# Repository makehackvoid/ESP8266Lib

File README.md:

ESP8266Lib
----------

This is MHV's library for the ESP8266. It's a group effort
and aims to make developing for the ESP8266 a little easier.

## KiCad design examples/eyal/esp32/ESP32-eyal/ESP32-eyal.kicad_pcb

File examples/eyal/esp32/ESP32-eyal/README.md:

I decided to make a PCB for my ESP32 things. I have many installed, each made differently. It is time to standardise them, hence this KiCAD (6) project.
======

I had the boards made by JLCPCB on 29/Feb/24, see the gerbers: gerbers-20240229-1703.zip

WARNING: Two issues with this version:
```
    1 - Solar charger requires a cap on the input.
    2 - The I2C lines incorrectly connect to pins 21/22, should be GPIO 21/22 (pins 33[SDA]/36[SCL]).
```

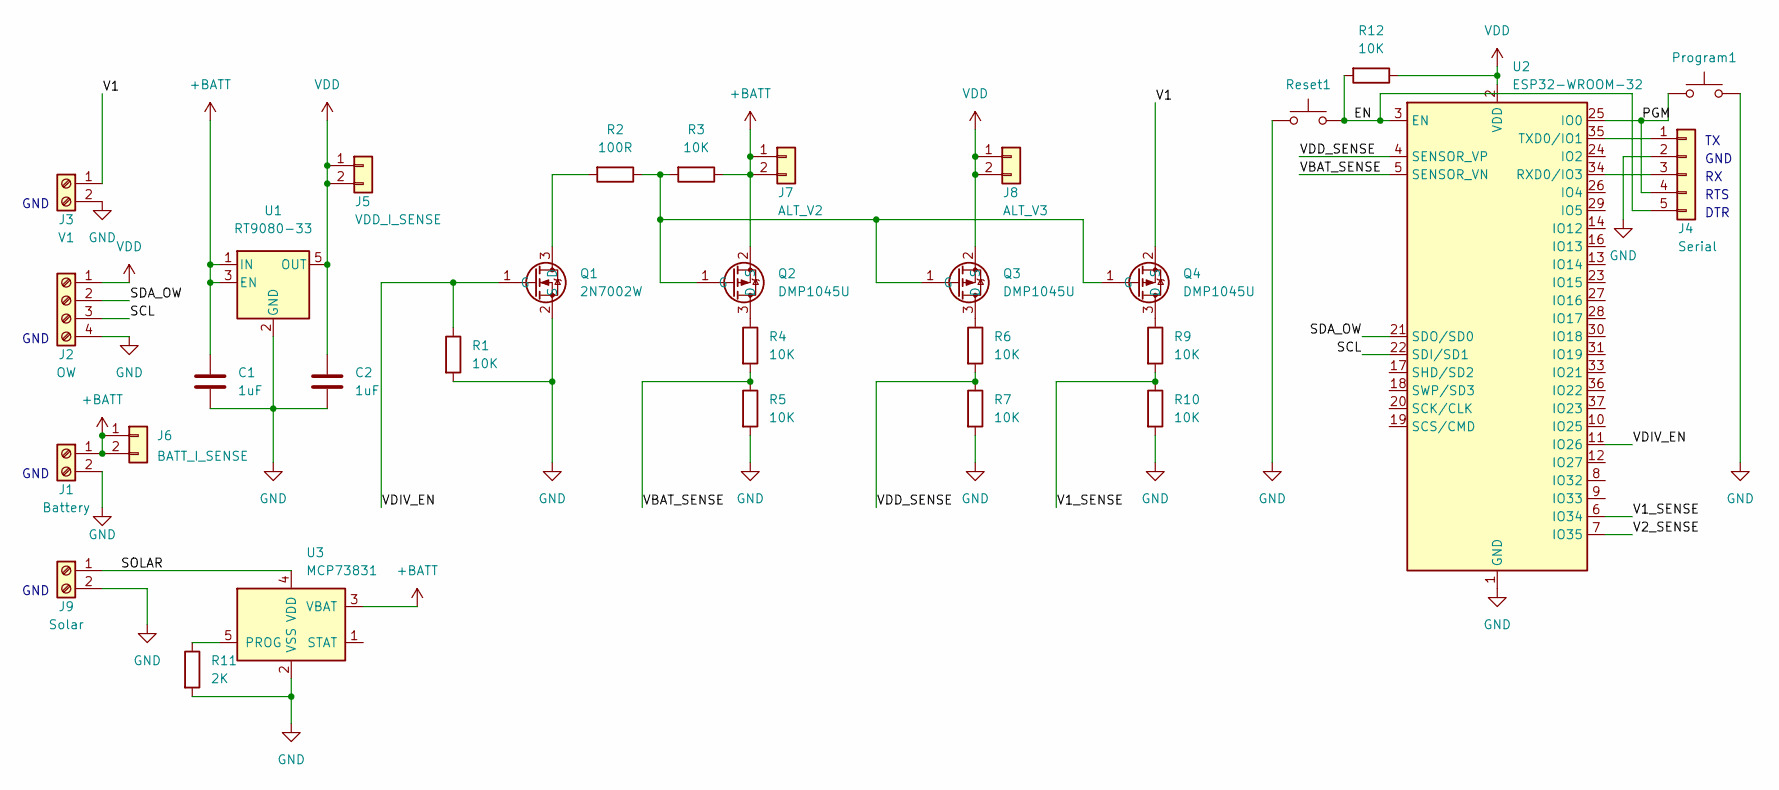
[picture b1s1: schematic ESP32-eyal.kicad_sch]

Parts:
C1, C2: 1uF; C_0805_2012Metric
J1: Battery; TerminalBlock_TE_282834-2_1x02_P2.54mm_Horizontal
J2: OW; TerminalBlock_TE_282834-4_1x04_P2.54mm_Horizontal
J3: V1; TerminalBlock_TE_282834-2_1x02_P2.54mm_Horizontal
J4: Serial; PinHeader_1x05_P2.54mm_Vertical
J5: VDD_I_SENSE; PinHeader_1x02_P2.54mm_Vertical
J6: BATT_I_SENSE; PinHeader_1x02_P2.54mm_Vertical
J7: ALT_V2; PinHeader_1x02_P2.54mm_Vertical
J8: ALT_V3; PinHeader_1x02_P2.54mm_Vertical
J9: Solar; TerminalBlock_TE_282834-2_1x02_P2.54mm_Horizontal
Program1: SW_Push; My_Switch
Q1: 2N7002W; SOT-23
Q2, Q3, Q4: DMP1045U; SOT-23
R1, R3, R4, R5, R6, R7, R9, R10, R12: 10K; R_0805_2012Metric
R2: 100R; R_0805_2012Metric
R11: 2K; R_0805_2012Metric
Reset1: SW_Push; My_Switch
U1: RT9080-33; SOT-23-5
U2: ESP32-WROOM-32
U3: MCP73831; SOT-23-5

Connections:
+BATT: C1.1, J1.1, J6.1, J6.2, J7.1, J7.2, Q2.2 (S), R3.1, U1.1 (IN), U1.3 (EN), U3.3 (VBAT)
/EN: J4.5, R12.2, Reset1.2, U2.3 (EN); also elsewhere on the board
/PGM: J4.4, Program1.1, U2.25 (IO0); also elsewhere on the board
/SCL: J2.3, U2.22 (SDI/SD1)
/SDA_OW: J2.2, U2.21 (SDO/SD0)
/SOLAR: J9.1, U3.4 (VDD); also elsewhere on the board
/V1: J3.1, Q4.2 (S)
/V1_SENSE: R9.2, R10.1, U2.6 (IO34)
/V2_SENSE: U2.7 (IO35)
/VBAT_SENSE: R4.2, R5.1, U2.5 (SENSOR_VN)
/VDD_SENSE: R6.2, R7.1, U2.4 (SENSOR_VP)
/VDIV_EN: Q1.1 (G), R1.1, U2.11 (IO26)
GND: C1.2, C2.2, J1.2, J2.4, J3.2, J4.2, J9.2, Program1.2, Q1.2 (S), R1.2, R5.2, R7.2, R10.2, R11.2, Reset1.1, U1.2 (GND), U2.1 (GND), U2.15 (GND), U2.38 (GND), U2.39 (GND), U3.2 (VSS); also elsewhere on the board
unnamed: J4.1, U2.35 (TXD0/IO1)
unnamed: J4.3, U2.34 (RXD0/IO3)
unnamed: Q1.3 (D), R2.2
unnamed: Q2.1 (G), Q3.1 (G), Q4.1 (G), R2.1, R3.2
unnamed: Q2.3 (D), R4.1
unnamed: Q3.3 (D), R6.1
unnamed: Q4.3 (D), R9.1
unnamed: R11.1, U3.5 (PROG)
VDD: C2.1, J2.1, J5.1, J5.2, J8.1, J8.2, Q3.2 (S), R12.1, U1.5 (OUT), U2.2 (VDD)

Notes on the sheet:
GND
DTR
RTS

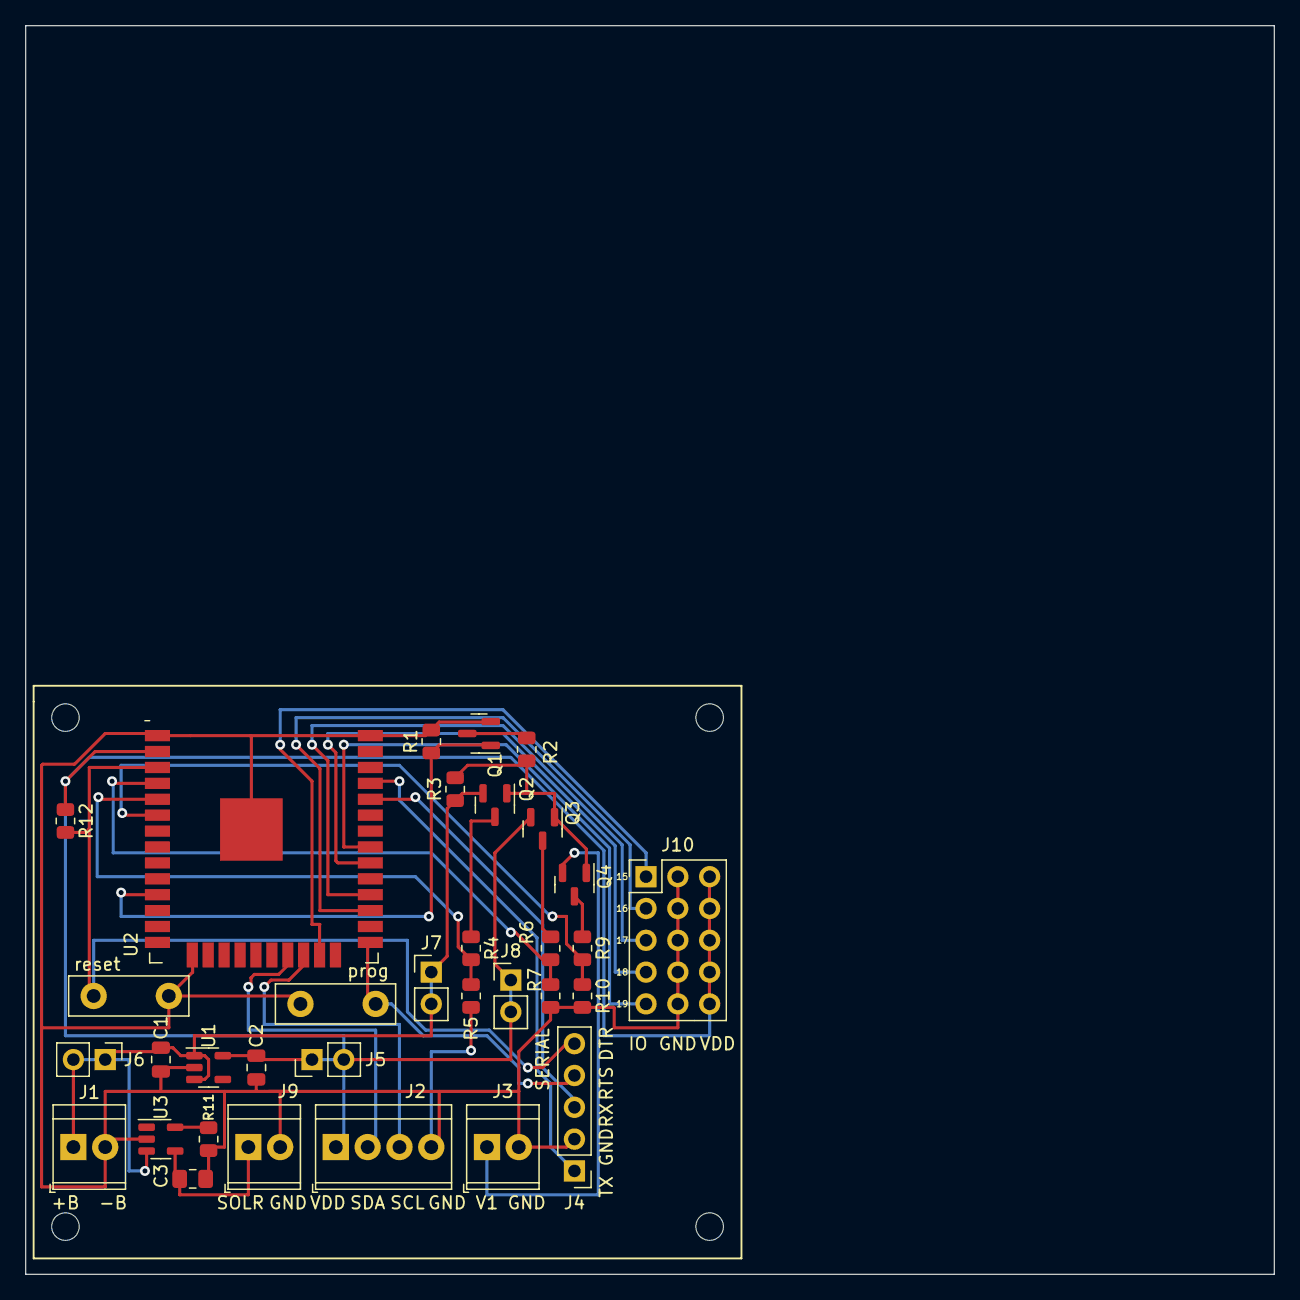
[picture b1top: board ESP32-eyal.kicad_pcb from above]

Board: 2 copper layers, 99.7 x 99.7 mm, 32 parts (0 on the bottom side), 21 nets.

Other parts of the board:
C3: 4.7uF; C_0805_2012Metric_Pad1.18x1.45mm_HandSolder
prog: SW_Push; My_Switch
reset: SW_Push; My_Switch

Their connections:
/EN: reset.2; also elsewhere on the board
/PGM: prog.1; also elsewhere on the board
/SOLAR: C3.2; also elsewhere on the board
GND: C3.1, prog.2, reset.1; also elsewhere on the board

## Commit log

2015-02-06 Readme added
2015-02-06 Initial Checkin
2015-02-07 Create test
2015-02-07 Delete test
    Remove unneeded test file.
2015-02-07 testing...
2015-02-07 still testing...
2015-02-08 Next test program.
2015-02-08 Show a good run.
2015-02-08 Try other quoting
2015-02-08 This is getting tired now...
2015-02-08 Added brief instructions
2015-02-08 format fixes
2015-02-08 reformat
2015-02-09 Another test program
2015-02-09 Add temp reading MQTT example
    MQTT temp read from ds18b20.
2015-02-09 A new fw build from tonight
2015-02-10 A new test program version (from Derryn)
2015-02-10 Rename firmware
2015-02-10 A simple rebooting test program
2015-02-13 An up-to-date firmware.
2015-02-13 Another version of the MQTT test program
2015-02-13 Another test program for ds18b20+MQTT
2015-02-13 A later fw (with node.compile)
2015-02-13 Explain
2015-02-14 Yet another MQTT test program
2015-02-19 This test proram does not write to flash, but reads from the broker.
2015-02-20 Clean up old test programs and check in what I consider an OK one that works.
2015-02-20 Oops, add missing modules
2015-02-23 Refactor the basic test programs
2015-02-23 Forgot to actually add the programms :-(
2015-02-24 Define test_count earlier
2015-02-25 Add an RTC example
2015-02-25 Update some READMEs
2015-03-04 Add a few more modules and update the MQTT+ds18b20 program
2015-03-04 Fix typos
2015-03-04 Missed one typo
2015-03-05 More ds3231 details
2015-03-05 Update and unify
2015-03-05 Add pca9555 module
2015-03-05 Add pca9555 to README
2015-03-06 Use timer. Handle more key combinations.
2015-03-06 Add module for at24c32 eeprom
2015-03-06 Fix reading hour
2015-03-14 Another mqtt example
2015-03-14 Fix spelling.
2015-03-14 Fix doco error
2015-04-08 A more recent ds3231 driver.
2015-04-08 A second try, with feeling...
2015-05-19 Added MSP430 temp read
2015-05-21 Add minimal uart code
2015-05-25 Current status of the app
2015-05-25 More README
2015-05-25 More doco
2015-05-25 More doco updates
2015-05-25 Add app_v1
2015-05-25 Correct program name
2015-05-25 Fix spelling
2015-08-02 Add a later version of the application
2015-09-04 New 'misc' directory
2015-09-04 dd the test program
2016-01-19 My experiment with RTOS SDK
2016-01-28 Later luas app and new SDK no-os version
2016-06-02 Add Arduino IDE example
2016-06-02 Read the DS18 earlier.
2016-06-03 Newer version of the sketch
2016-06-05 Read vdd, then some cosmo
2016-06-09 Implement timed wakeups
2016-06-10 Allow multiple sensors
2016-06-11 Small WiFi setup change
2016-06-30 Update to latest version
2016-07-01 Add missing files (what went wrong?)
2016-07-06 minor cleanup
2016-11-18 Update to latest and fill in the README.
2016-11-18 Add an explanatory comment
2016-11-18 Add a comment
2016-12-08 update to latest version, mainly adding mpe280.
2016-12-08 Add new modules
2016-12-20 Added trace feature. New wifi setup. General update.
2016-12-20 Minor doco adjustment
2016-12-20 Typo
2016-12-20 Fix one program name
2016-12-28 Some recent updates
2017-01-02 Add mqtt. Fix rtctime usage. Other minior fixes.
2017-01-02 Minor fix
2017-01-03 NodeMCU/dev quietly changed how UDP works :-(
2017-01-03 Tested TCP too.
2017-01-04 Use new wifi.sta.config style
2017-01-11 Fix a wifi problem. Improve response to connection failure.
2017-01-11 Import recent changes. Add error checking to the upload.
2017-01-11 Minimal cosmetics
2017-01-12 Update i0.lua
    Remove stray duplicated line
2017-01-13 Cosmo
2017-01-13 More cleanup
2017-01-29 Update to current
2017-03-19 Update to the latest version (many adjustments)
2017-03-19 Add missed updated module
2017-05-13 Add esp32 example
2017-05-13 Some cleanup.
2017-05-17 Ass IDF example
2017-05-17 Reorg
2017-05-17 Mention the esp32 in the doco
2017-05-18 Update to latest code
2017-05-19 Update example
2017-05-20 Update repository, now running at 240MHz.
2017-05-20 Sort out rssi.
2017-05-27 Add i2c bme280. Not yet working.
2017-05-30 Add onewire and some restructuring. Still work in progress.
2017-05-31 Add adc reading
2017-06-01 Still working at reliable onewire. Wondering if using RMT a must.
2017-06-02 Re-read wo as timing issues still cause intemittent failures. Added ow crc check.
2017-06-03 Run as a task with high priority to reduce timing issues (still not perfect).
2017-06-04 More work on bme280.
2017-06-04 Add rest of compensation routines.
2017-06-05 More cleanup.bme280 seems to be more stable now, onewire timing still problematic.
2017-06-07 More debugging.
2017-06-08 Still fine tuning one wire.
2017-06-13 Sorted out timing issues.
2017-06-13 Push some small changes.
2017-06-13 Set wakeup delay from default config
2017-06-14 Reorg adc module.
2017-06-15 Some cleanup. Some reorg.
2017-06-20 Add TSENS tracking. Use new (fixed) gettimeofday().
2017-06-21 Add a simple wifi test
2017-06-21 Try setting channel and use nvs.
2017-06-25 Sort out bme280 initial failure
2017-06-28 Some minor fiddling for tracking clock rate vs. temperature (TSENS).
2017-07-05 Add a simple signal strength monitor, used to test antennas.
2017-07-13 Correct one comment.
2017-07-13 Add support for Derryn's board battery voltage reading.
2017-07-13 Uncomment stuff that was disabled to fit in a 512KB module.
2017-07-13 Add support for Derryn's battery voltage reading.
2017-07-13 Add a name for gpio5 pin.
2017-09-11 Check in recent changes. New adc API. Still tracking clocks.
2017-09-11 Add latest config
2017-10-19 Use new manifests
2017-10-19 Sketch for MHV clock project.
2017-10-19 nvs_flash_init now required for esp_wifi_init.
2017-10-24 Minor adjustment of headers.
2017-11-06 Bring git up-to-date with minor changes
2017-11-10 Cosmo - clean device enable/diable sections
2018-02-07 Try to sort out missing files.
2018-04-28 Add a test program
2018-04-28 Update comment.
2018-04-29 Fix real wifi.suspend() call
2018-04-29 Show startup reason/cause etc.
2018-06-21 Check in latest updates, mostly wifi tweaking.
2018-08-09 Check in latest verion
2018-08-10 Adjust esp config
2018-08-10 Add a download utility
2018-08-10 Move some doco to proper subdir
2018-08-10 Fix bug with multiple device types
2018-08-15 Some cleanu. Fix bug in ds18b20 reading.
2018-08-16 Add pinout
2018-09-17 dos2unix all Split first.lua Better timing in reading ds18b20 (convert all at once)
2019-07-22 An initial arduino sketch for using the INA219 current meteri. I run it on an ESP8266.
2019-07-22 Fix minor calculation
2019-07-28 A simple sketch for using the ina219 current sensor, with a modified Adafruit library.
2019-07-28 Some renaming for clarity, more debug logging.
2019-07-30 Describe the new ina219 and related library better.
2019-07-30 Check in latest changes. ina219/ina219.ino: use 'double' for mAh/mWh accumulator instead of every reading, reset the calibration register every period (1 second here, about 2000 readings) Adafruit_IN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
2020-08-31 Up from IDF v3.0 to v4.1
2021-10-31 Add a test sketch to see the excessive time Arduino takes to connect to WiFi.
2021-10-31 Add a wifi connection timing test using IDF.
2021-10-31 Reorder last items.
2021-11-02 Remove some special needs.
2021-11-11 Add a small ULP project for ULP power usage test.
2021-11-11 Update the README
2021-11-11 Add a sketch of the project board
2021-11-13 Add another picture
2021-11-13 use uint32_t instead of ulong
2022-03-25 New version with ULP
2022-03-25 Mention new verion
2022-03-25 Fix README
2024-02-23 A KiCAD project where I learn to produce an ESP32 PCB.
2024-02-23 Files added to the wrong place.
2024-02-23 My KiCAD project of an ESP32 board.
2024-02-23 Add a REDME
2024-02-23 Add pdf of files
2024-02-24 Commit recent updates
2024-02-25 Say this project uses KiCAD 6 (not 7).
2024-02-25 some minor pcb adjustments (clear DRC warnings).
2024-02-28 Same ESP pcb with many other small sot-23 adapters.
2024-02-29 Latest version, with mounting holes and a sea of small utility modules.
2024-03-04 Add a Work Sheet.
2024-03-05 Add the gerbers as manufactured.
2024-03-09 Some adjustments in version 2
2024-04-24 Add warning about mistakes.
2024-04-24 Better format
2024-04-24 Minor spelling
